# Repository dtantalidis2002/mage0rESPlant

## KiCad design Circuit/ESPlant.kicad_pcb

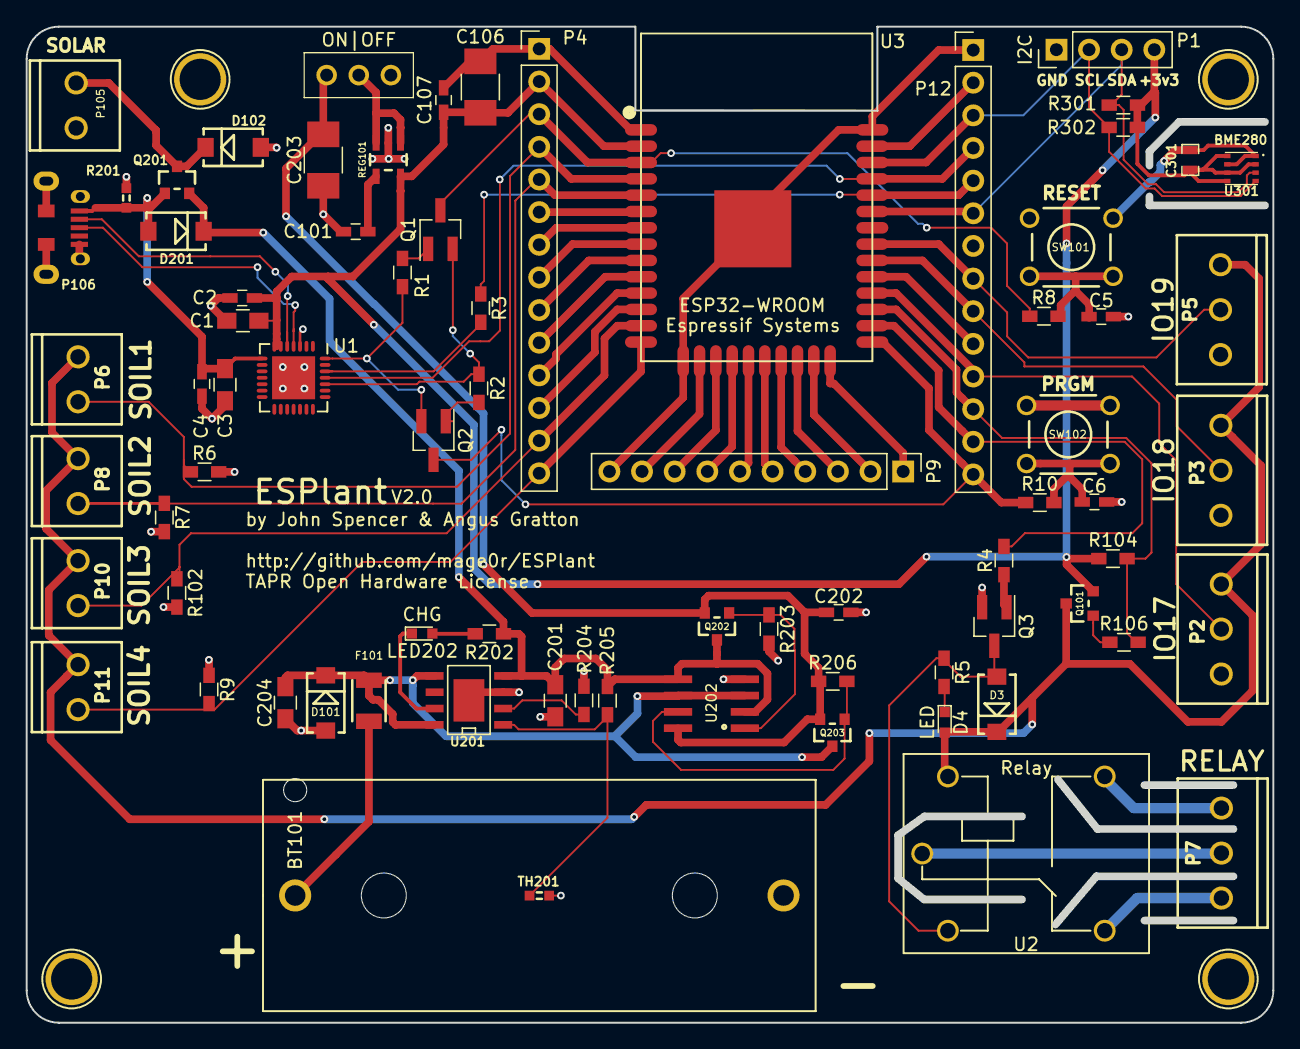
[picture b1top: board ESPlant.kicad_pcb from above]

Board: 2 copper layers, 97.0 x 77.5 mm, 79 parts (0 on the bottom side), 66 nets.

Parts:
BT101: Battery; CR123_Holder
C1, C3, C201, C204: 10uF; C_0805_HandSoldering
C2, C4: 0.1uF; C_0603_HandSoldering
C5, C6: 1uF; C_0603_HandSoldering
C101, C107, C202: 100nF; C_0603_HandSoldering
C106: 100uF; C_1210_HandSoldering
C203: 100uF 16V X5R; C_1210_HandSoldering
C301: 1uF; 0603_CAP
D3, D101, D102, D201: SS14; DIODE_SMA
D4: LED; LED_0603
F101: 1A PTC; 1210
LED202: CHG; LED_0603
MH101, MH102, MH103, MH104: TEST_1P; 1pin
P1: I2C; Pin_Header_Straight_1x04_Pitch2.54mm
P2: IO17; SCREWTERMINAL-3.5MM-3
P3: IO18; SCREWTERMINAL-3.5MM-3
P4, P12: CONN_01X14; Pin_Header_Straight_1x14_Pitch2.54mm
P5: IO19; SCREWTERMINAL-3.5MM-3
P6: SOIL1; SCREWTERMINAL-3.5MM-2
P7: RELAY; SCREWTERMINAL-3.5MM-3
P8: SOIL2; SCREWTERMINAL-3.5MM-2
P9: CONN_01X10; Pin_Header_Straight_1x10_Pitch2.54mm
P10: SOIL3; SCREWTERMINAL-3.5MM-2
P11: SOIL4; SCREWTERMINAL-3.5MM-2
P105: SOLAR; SCREWTERMINAL-3.5MM-2
P106: USB_5PIN_SHELL; USB-MICRO-5pin_PTHMOUNT
Q1, Q2: S8050; SOT-23_Handsoldering
Q3: 2N7002; SOT-23_Handsoldering
Q101, Q201, Q202, Q203: FDN340P; SOT23_FET
R1, R2: 12K; R_0603_HandSoldering
R3, R8, R10: 470R; R_0603_HandSoldering
R4, R5, R106, R202: 1K; R_0603_HandSoldering
R6, R7, R9, R102, R203, R206: 100K; R_0603_HandSoldering
R104: 10K; R_0603_HandSoldering
R201: 1K; 0603
R204: 3.6K; R_0603_HandSoldering
R205: 7.15K; R_0603_HandSoldering
R301, R302: 4.7K; R_0603_HandSoldering
REG101: SPX3819M5-3.3; SOT23-5
SW101: RESET; SW_PUSHBUTTON_PTH
SW102: PRGM; SW_PUSHBUTTON_PTH
SW104: ON|OFF; SS12D00
TH201: 10K NTC; 0603
U1: CP2102; QFN-28-1EP_5x5mm_Pitch0.5mm
U2: Relay; SPDT_Songle_Relay
U3: ESP32-WROOM
U201: CN3063; CN3063_SOIC8_EP
U202: MCP6002; SO08_4mm
U301: BME280

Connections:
+3V3: C1.1, C2.1, C106.1, C107.1, C301.1, P1.4, P4.2, Q101.S, R104.1, R301.1, R302.1, REG101.5, U1.6, U1.7, U3.2, U301.2, U301.5, U301.6, U301.8
/BAT+: BT101.1, F101.1
/CLK: P9.5, U3.20
/CMD: P9.6, U3.19
/DTR: Q2.2, R1.2, U1.28
/EN: P4.3, Q1.3, R8.1, U3.3
/I2C_SCL: P1.2, P12.3, R302.2, U3.36, U301.4
/I2C_SDA: P1.3, P12.6, R301.2, U3.33, U301.3
/IO0: P12.14, Q2.3, R10.1, U3.25
/IO2: P9.1, U3.24
/IO4: P12.13, R4.2, U3.26
/IO5: P12.10, U3.29
/IO12: P4.14, P11.2, R9.1, U3.14
/IO13: P9.9, U3.16
/IO14: P4.13, P10.2, R102.1, U3.13
/IO15: P9.2, U3.23
/IO16: P12.12, R104.2, R106.2, U3.27
/IO17: P2.2, P12.11, U3.28
/IO18: P3.2, P12.9, U3.30
/IO19: P5.2, P12.8, U3.31
/IO23: P12.2, U3.37
/IO25: P4.10, U3.10
/IO26: P4.11, U3.11
/IO27: P4.12, U3.12
/IO32: P4.8, U3.8
/IO33: P4.9, U3.9
/IO34: P4.6, U3.6
/IO35: P4.7, U3.7
/Power/GBAT: Q203.G, R206.2, U202.7
/Power/GIN: Q202.G, R203.1, U202.1
/Power/SOLAR_IN: D102.K, P105.1, Q201.D
/Power/VBAT: C204.1, D101.K, F101.2, Q203.D, U201.5, U201.8, U202.3, U202.6
/Power/VIN: C201.1, D201.K, Q201.S, Q202.D, R202.1, R205.1, U201.4, U202.2, U202.5
/Power/~CHRG: LED202.1, U201.7
/RTS: Q1.2, R2.2, U1.24
/RXD: P12.4, U1.25, U3.35
/SD0: P9.4, U3.21
/SD1: P9.3, U3.22
/SD2: P9.8, U3.17
/SD3: P9.7, U3.18
/SOIL1: P4.4, P6.2, R6.1, U3.4
/SOIL2: P4.5, P8.2, R7.1, U3.5
/TXD: P12.5, R3.1, U3.34
/USB_D+: P106.3, U1.4
/USB_D-: P106.2, U1.5
/USB_VCC: C3.1, C4.1, D201.A, P106.1, Q201.G, R201.1, U1.8
/VCC_SENS: D3.K, D4.2, P2.3, P3.3, P5.3, P6.1, P8.1, P10.1, P11.1, Q101.D, U2.1
/VOUT: C202.1, C203.2, Q202.S, Q203.S, R206.1, SW104.1, U202.8
/VSWITCHED: REG101.1, REG101.3, SW104.2
GND: BT101.2, C1.2, C2.2, C3.2, C4.2, C5.2, C6.2, C101.2, C106.2, C107.2, C201.2, C202.2, C203.1, C204.2, C301.2, D101.A, D102.A, P1.1, P2.1, P3.1, P4.1, P5.1, P9.10, P12.1, P105.2, P106.5, P106.SHLD, Q3.2, R6.2, R7.2, R9.2, R102.2, R201.2, R203.2, R204.2, REG101.2, SW101.1, SW102.1, TH201.2, U1.3, U1.29, U3.1, U3.15, U3.38, U3.39, U201.3, U201.PAD, U202.4, U301.1, U301.7
unnamed: C5.1, R8.2, SW101.2
unnamed: C6.1, R10.2, SW102.2
unnamed: C101.1, REG101.4
unnamed: D3.A, Q3.3, R5.1, U2.2
unnamed: D4.1, R5.2
unnamed: LED202.2, R202.2
unnamed: P7.1, U2.5
unnamed: P7.2, U2.3
unnamed: P7.3, U2.4
unnamed: Q1.1, R1.1
unnamed: Q2.1, R2.1
unnamed: Q3.1, R4.1
unnamed: Q101.G, R106.1
unnamed: R3.2, U1.26
unnamed: R204.1, U201.2
unnamed: R205.2, TH201.1, U201.1

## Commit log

2017-03-09 ESP32 Version
2017-03-09 Added pdf
2017-03-14 Updated pcb.
    Completed a missing track.
    Added some ground plane to the regulator.
    Changed some silkscreen test.
2018-03-14 Updates, I guess

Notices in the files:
Circuit/ESPlant.kicad_pcb:
TAPR Open Hardware License
